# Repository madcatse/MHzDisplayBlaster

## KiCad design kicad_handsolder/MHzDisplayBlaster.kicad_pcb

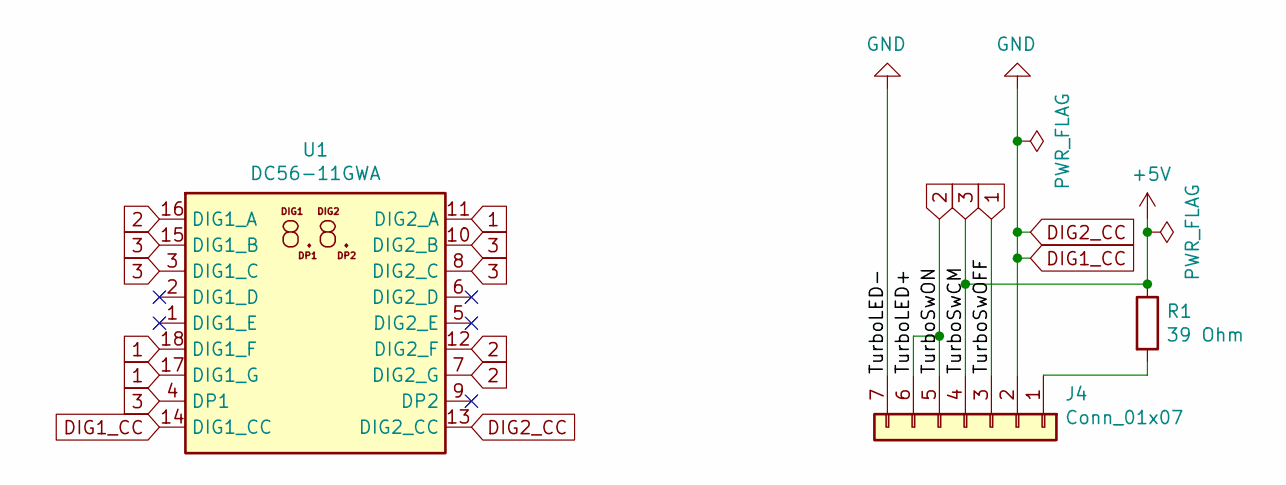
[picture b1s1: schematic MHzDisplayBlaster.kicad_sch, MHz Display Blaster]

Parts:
J4: Conn_01x07; PinHeader_1x07_P2.54mm_Vertical
R1: 39 Ohm; R_Axial_DIN0207_L6.3mm_D2.5mm_P10.16mm_Horizontal
U1: DC56-11GWA; DA56-11CGKWA

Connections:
1: J4.3, U1.11 (DIG2_A), U1.17 (DIG1_G), U1.18 (DIG1_F)
2: J4.5, J4.6, U1.7 (DIG2_G), U1.12 (DIG2_F), U1.16 (DIG1_A)
3: J4.4, R1.1, U1.3 (DIG1_C), U1.4 (DP1), U1.8 (DIG2_C), U1.10 (DIG2_B), U1.15 (DIG1_B)
DIG1_CC: J4.2, J4.7, U1.13 (DIG2_CC), U1.14 (DIG1_CC)
unnamed: J4.1, R1.2

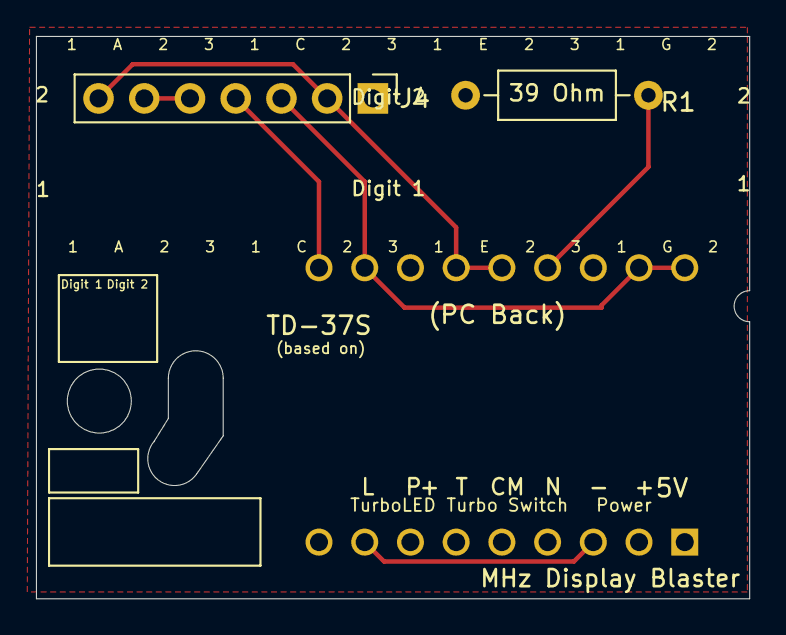
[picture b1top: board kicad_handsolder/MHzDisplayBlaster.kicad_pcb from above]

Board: 2 copper layers, 39.6 x 31.2 mm, 3 parts (1 on the bottom side), 5 nets.

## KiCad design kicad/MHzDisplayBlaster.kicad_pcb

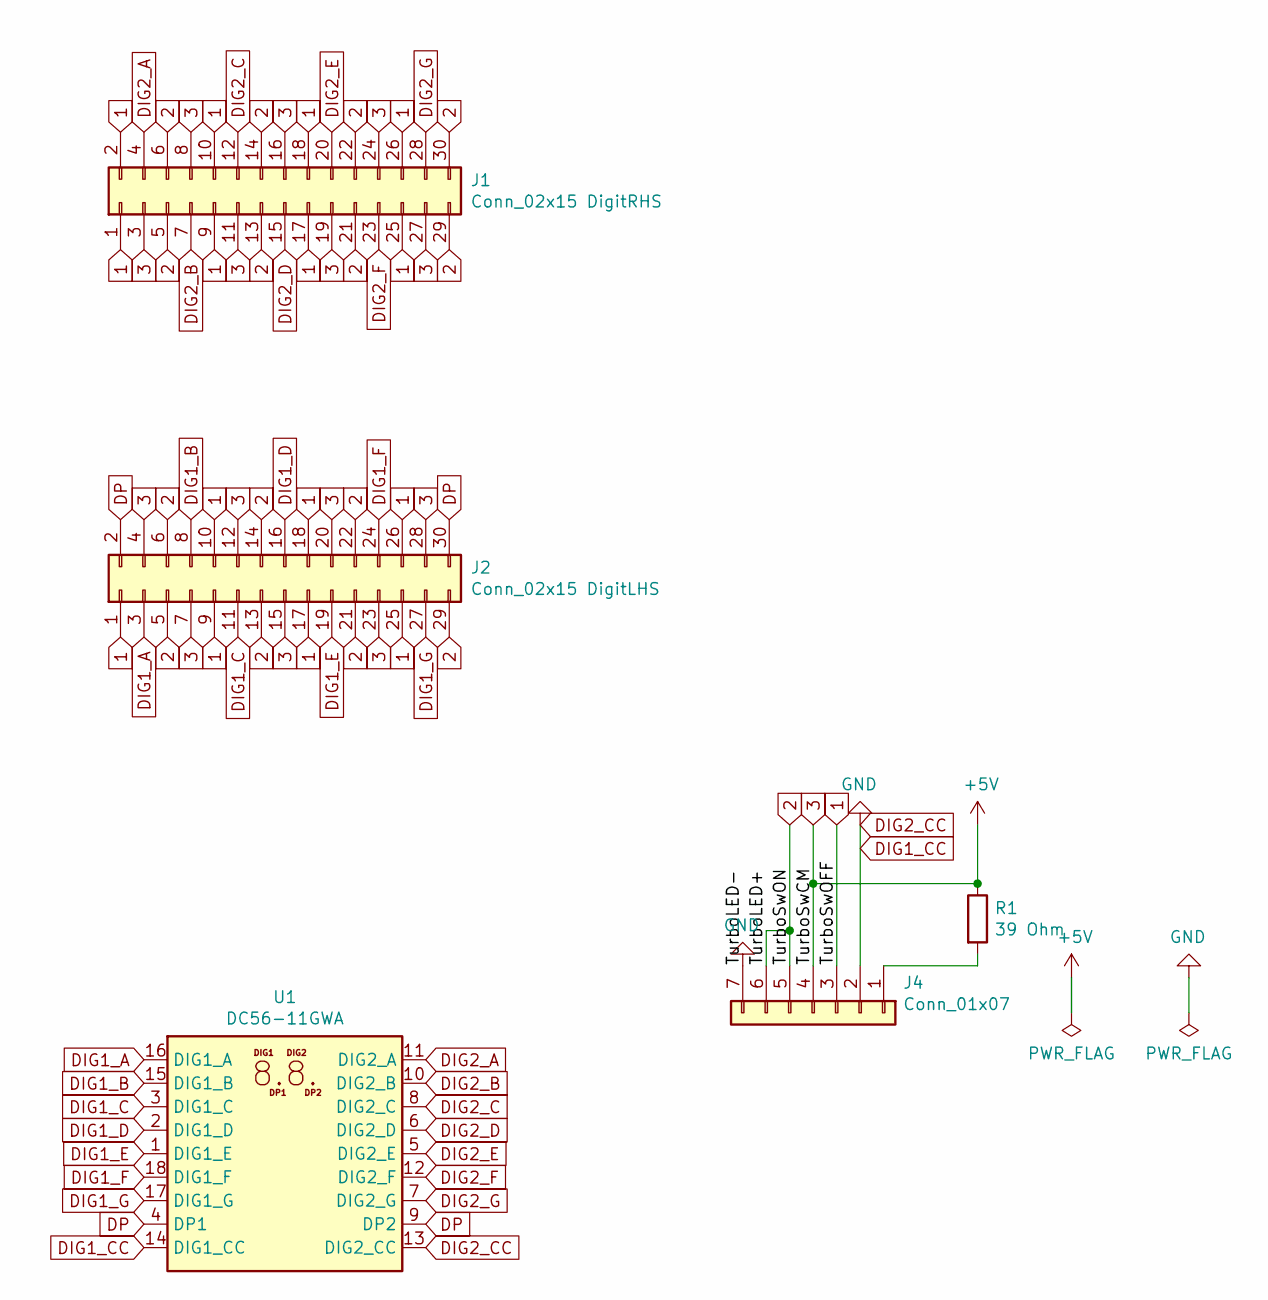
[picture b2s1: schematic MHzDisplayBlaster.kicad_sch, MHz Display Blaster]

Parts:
J1: Conn_02x15 DigitRHS; PinHeader_2x15_P2.54mm_Vertical
J2: Conn_02x15 DigitLHS; PinHeader_2x15_P2.54mm_Vertical
J4: Conn_01x07; PinHeader_1x07_P2.54mm_Vertical
R1: 39 Ohm; R_Axial_DIN0207_L6.3mm_D2.5mm_P10.16mm_Horizontal
U1: DC56-11GWA; DA56-11CGKWA

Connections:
1: J1.1, J1.2, J1.9, J1.10, J1.17, J1.18, J1.25, J1.26, J2.1, J2.9, J2.10, J2.17, J2.18, J2.25, J2.26, J4.3
2: J1.5, J1.6, J1.13, J1.14, J1.21, J1.22, J1.29, J1.30, J2.5, J2.6, J2.13, J2.14, J2.21, J2.22, J2.29, J4.5, J4.6
3: J1.3, J1.8, J1.11, J1.16, J1.19, J1.24, J1.27, J2.4, J2.7, J2.12, J2.15, J2.20, J2.23, J2.28, J4.4, R1.1
DIG1_A: J2.3, U1.16 (DIG1_A)
DIG1_B: J2.8, U1.15 (DIG1_B)
DIG1_C: J2.11, U1.3 (DIG1_C)
DIG1_CC: J4.2, J4.7, U1.13 (DIG2_CC), U1.14 (DIG1_CC)
DIG1_D: J2.16, U1.2 (DIG1_D)
DIG1_E: J2.19, U1.1 (DIG1_E)
DIG1_F: J2.24, U1.18 (DIG1_F)
DIG1_G: J2.27, U1.17 (DIG1_G)
DIG2_A: J1.4, U1.11 (DIG2_A)
DIG2_B: J1.7, U1.10 (DIG2_B)
DIG2_C: J1.12, U1.8 (DIG2_C)
DIG2_D: J1.15, U1.6 (DIG2_D)
DIG2_E: J1.20, U1.5 (DIG2_E)
DIG2_F: J1.23, U1.12 (DIG2_F)
DIG2_G: J1.28, U1.7 (DIG2_G)
DP: J2.2, J2.30, U1.4 (DP1), U1.9 (DP2)
unnamed: J4.1, R1.2

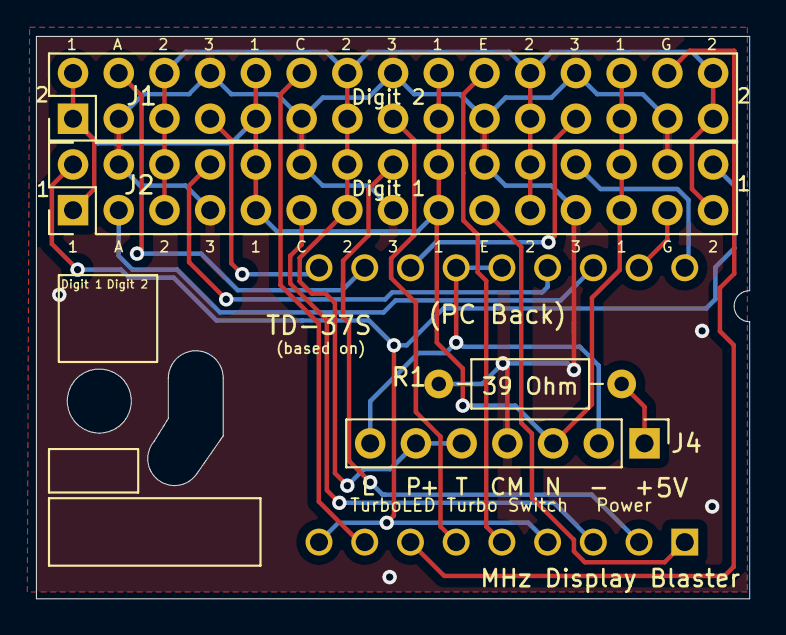
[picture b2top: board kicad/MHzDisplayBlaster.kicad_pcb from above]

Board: 2 copper layers, 39.6 x 31.2 mm, 5 parts (1 on the bottom side), 20 nets.

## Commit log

2025-08-05 Update KICAD version
2025-08-05 Self-made 4.7 - 7.4
